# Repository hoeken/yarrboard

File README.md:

# Yarrboard

A collection of open hardware projects for automation projects on your boat.

The project is broken into a few different repositories:

* [FrothFET](https://github.com/hoeken/frothfet) - 8 Channel Digital Switching board with pwm + load monitoring
* [FrothFET Firmware](https://github.com/hoeken/frothfet-firmware) - Firmware for the FrothFET board
* [Brineomatic](https://github.com/hoeken/brineomatic) - Watermaker Controller
* [Brineomatic Firwmare](https://github.com/hoeken/brineomatic) - Firmware for the Brineomatic board
* [SendIt](https://github.com/hoeken/sendit) - 8 channel sensor multitool board
* [SendIt Firwmare](https://github.com/hoeken/sendit-firmware) - Firmware for the SendIt board
* [Yarrboard Framework](https://github.com/hoeken/YarrboardFramework) - Common framework that all the boards run on
* [SignalK Plugin](https://github.com/hoeken/signalk-yarrboard-plugin) - Plugin for SignalK integration
* [Yarrboard Client](https://github.com/hoeken/yarrboard-client) - JS client for controlling a board over websocket

## Interface

Since it is based on the esp32, the main communication method is over WiFi.  Setup, config, and control are very easy using the built-in web portal.  Just point your phone to the url of the board and you're good to go.  Typically this is http://yarrboard.local or http://yarrboard.  You can change this hostname in the settings, or use the IP address instead.

## SignalK

There is also a plugin for integration with SignalK, so you can have your data all in one place.  It supports two way comms, so you can use SignalK and Node-RED to turn your loads on or off.

The plugin for SignalK is called [signalk-yarrboard-plugin](https://github.com/hoeken/signalk-yarrboard-plugin)

## How To Get One

No production as of right now, but possibly in the future.  It is 100% open source, so its possible to order PCBs, parts, and DIY your own board if you like.  There is the potential of partnering with the right person to take care of the manufacturing side of things, or you could make and sell your own - its open source after all!

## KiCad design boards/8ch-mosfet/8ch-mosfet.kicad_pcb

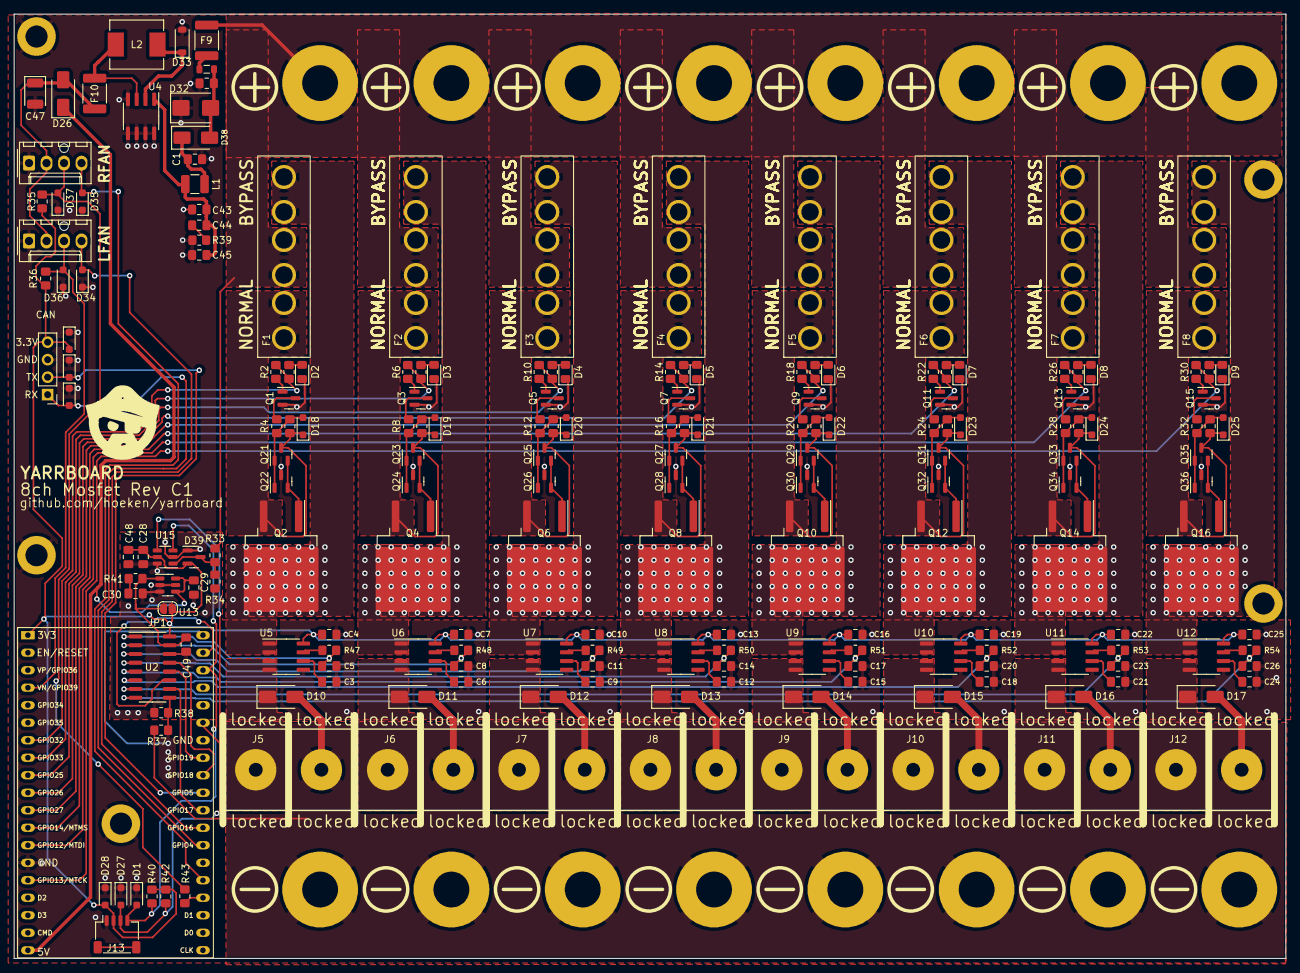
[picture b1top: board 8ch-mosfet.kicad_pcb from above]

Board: 2 copper layers, 184.5 x 137.0 mm, 204 parts (0 on the bottom side), 126 nets.

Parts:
C1: 470nF/50v; C_0805_2012Metric_Pad1.18x1.45mm_HandSolder
C2: 10nF; C_0805_2012Metric_Pad1.18x1.45mm_HandSolder
C3, C6, C9, C12, C15, C18, C21, C24: 1nF; C_0805_2012Metric_Pad1.18x1.45mm_HandSolder
C4, C7, C10, C13, C16, C19, C22, C25, C28, C29, C30, C49: 100nF; C_0805_2012Metric_Pad1.18x1.45mm_HandSolder
C5, C8, C11, C14, C17, C20, C23, C26: 4.7nF; C_0805_2012Metric_Pad1.18x1.45mm_HandSolder
C43: 1uF/50v; C_0805_2012Metric_Pad1.18x1.45mm_HandSolder
C44: 4.7uF/50v; C_0805_2012Metric_Pad1.18x1.45mm_HandSolder
C45: 22uF/35v; C_0805_2012Metric_Pad1.18x1.45mm_HandSolder
C47: 100uF / 10v; CP_EIA-3528-21_Kemet-B
C48: 10uF; C_0805_2012Metric_Pad1.18x1.45mm_HandSolder
D1, D27, D28, D29, D30, D31, D34, D35, D36, D37: PESD3V3L1BA; D_SOD-323_HandSoldering
D2, D3, D4, D5, D6, D7, D8, D9: LED; LED_0805_2012Metric_Pad1.15x1.40mm_HandSolder
D10, D11, D12, D13, D14, D15, D16, D17: SS16; D_SMA
D18, D19, D20, D21, D22, D23, D24, D25: 15V; D_SOD-323_HandSoldering
D26, D38: SX33L; D_SMA
D32: SMBJ30CA; D_SMB
D33: DSK24; D_SOD-123
D39: BAT54S; SOT-23
F1, F2, F3, F4, F5, F6, F7, F8: 25A; ATC Bypass Fuse
F9: mSMD050-60V; Fuse_1812_4532Metric_Pad1.30x3.40mm_HandSolder
F10: mSMD110; Fuse_1812_4532Metric_Pad1.30x3.40mm_HandSolder
FB7: GZ2012D601TF; L_0805_2012Metric
H1, H2, H3, H4, H5: MountingHole; MountingHole_3.2mm_M3_DIN965_Pad
J3: Screw_Terminal_01x08; Busbar 1x9 .375in
J5, J6, J7, J8, J9, J10, J11, J12: Screw_Terminal_01x02; Molex 1x02 .375
J13: I2C; JST_SH_SM04B-SRSS-TB_1x04-1MP_P1.00mm_Horizontal
J14: N2K; PinHeader_1x04_P2.54mm_Vertical
JP1: SolderJumper_2_Open; SolderJumper-2_P1.3mm_Open_RoundedPad1.0x1.5mm
L1: CBC3225T100KR; L_1210_3225Metric
L2: SMMS0650-680M; L_Chilisin_BMRB00060650
LOGO: Logo Small
M1, M2: Fan_4pin; Molex 0470531000
Q1, Q3, Q5, Q7, Q9, Q11, Q13, Q15: 2N7002; SOT-23
Q2, Q4, Q6, Q8, Q10, Q12, Q14, Q16: IPB110P06LM; TO-263-2
Q21, Q23, Q25, Q27, Q29, Q31, Q33, Q35: BC846; SOT-23
Q22, Q24, Q26, Q28, Q30, Q32, Q34, Q36: BC856; SOT-23
R1, R5, R9, R13, R17, R21, R25, R29, R35, R36, R47, R48, R49, R50, R51, R52, R53, R54: 1k; R_0805_2012Metric_Pad1.20x1.40mm_HandSolder
R2, R6, R10, R14, R18, R22, R26, R30: 220R; R_0805_2012Metric_Pad1.20x1.40mm_HandSolder
R3, R7, R11, R15, R19, R23, R27, R31: 27k; R_0805_2012Metric_Pad1.20x1.40mm_HandSolder
R4, R8, R12, R16, R20, R24, R28, R32: 4.7k; R_0805_2012Metric_Pad1.20x1.40mm_HandSolder
R33: 300K 0.1%; R_0805_2012Metric_Pad1.20x1.40mm_HandSolder
R34: 22K 0.1%; R_0805_2012Metric_Pad1.20x1.40mm_HandSolder
R37, R38, R43: 0R; R_0805_2012Metric_Pad1.20x1.40mm_HandSolder
R39: 4.7R; R_0805_2012Metric_Pad1.20x1.40mm_HandSolder
R40, R42: 2.2k; R_0805_2012Metric_Pad1.20x1.40mm_HandSolder
R41: 10k; R_0805_2012Metric_Pad1.20x1.40mm_HandSolder
U1: ESP32-DEVKITC; ESP32-DevKitC
U2: MCP3208; SOIC-16_3.9x9.9mm_P1.27mm
U4: XL1509-5.0; SOIC-8_3.9x4.9mm_P1.27mm
U5, U6, U7, U8, U9, U10, U11, U12: ACS725xLCTR-20AU; ACS7XX
U13: MCP1502-33; SOT-23-6
U15: MCP3425A0T-ECH; SOT-23-6
locked: Screw_Terminal_01x08; Busbar 1x9 .375in

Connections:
+3.3V: C4.1, C7.1, C10.1, C13.1, C16.1, C19.1, C22.1, C25.1, C28.1, C48.1, D28.2 (A2), D31.2 (A2), D39.2 (K), J13.2, J14.4, JP1.2 (B), R35.2, R36.2, R40.2, R42.2, U1.1 (3V3), U2.16 (Vdd), U5.8 (VCC), U6.8 (VCC), U7.8 (VCC), U8.8 (VCC), U9.8 (VCC), U10.8 (VCC), U11.8 (VCC), U12.8 (VCC), U15.5 (Vdd)
+5V: C47.1, D26.2 (A), F10.1, M1.2 (+), M2.2 (+)
+24V: F1.2, F2.2, F3.2, F4.2, F5.2, F6.2, F7.2, F8.2, F9.2, J3.1, J3.2, J3.3, J3.4, J3.5, J3.6, J3.7, J3.8, R33.2
/ADC/A0: C5.1, R47.1, U2.1 (CH0)
/ADC/A1: C8.1, R48.1, U2.2 (CH1)
/ADC/A2: C11.1, R49.1, U2.3 (CH2)
/ADC/A3: C14.1, R50.1, U2.4 (CH3)
/ADC/A4: C17.1, R51.1, U2.5 (CH4)
/ADC/A5: C20.1, R52.1, U2.6 (CH5)
/ADC/A6: C23.1, R53.1, U2.7 (CH6)
/ADC/A7: C26.1, R54.1, U2.8 (CH7)
/CHANNEL 0/PWM: R1.2, R2.1, U1.7 (GPIO32)
/CHANNEL 1/PWM: R5.2, R6.1, U1.8 (GPIO33)
/CHANNEL 2/PWM: R9.2, R10.1, U1.9 (GPIO25)
/CHANNEL 3/PWM: R13.2, R14.1, U1.10 (GPIO26)
/CHANNEL 4/PWM: R17.2, R18.1, U1.11 (GPIO27)
/CHANNEL 5/PWM: R21.2, R22.1, U1.12 (GPIO14)
/CHANNEL 6/PWM: R25.2, R26.1, U1.13 (GPIO12)
/CHANNEL 7/PWM: R29.2, R30.1, U1.15 (GPIO13)
CAN_RX: D29.2 (A2), J14.1, U1.26 (GPIO4)
CAN_TX: D30.2 (A2), J14.2, U1.29 (GPIO5)
ESP32_5V: C29.1, D26.1 (K), U1.19 (5V0), U13.4 (~SHDN), U13.6 (VDD)
FAN_PWM1: D34.2 (A2), M2.4 (PWM), U1.27 (GPIO16)
FAN_PWM2: D35.2 (A2), M1.4 (PWM), U1.24 (GPIO2)
FAN_TACH1: D36.2 (A2), M2.3 (Tacho), R36.1, U1.4 (GPIO39)
FAN_TACH2: D37.2 (A2), M1.3 (Tacho), R35.1, R43.2
GNDA: C3.2, C4.2, C5.2, C6.2, C7.2, C8.2, C9.2, C10.2, C11.2, C12.2, C13.2, C14.2, C15.2, C16.2, C17.2, C18.2, C19.2, C20.2, C21.2, C22.2, C23.2, C24.2, C25.2, C26.2, C28.2, C29.2, C30.2, C48.2, C49.2, D39.1 (A), R34.1, R38.1, U2.14 (AGND), U5.5 (GND), U6.5 (GND), U7.5 (GND), U8.5 (GND), U9.5 (GND), U10.5 (GND), U11.5 (GND), U12.5 (GND), U13.2 (GND), U13.3 (GND), U13.5 (GND), U15.2 (Vss), U15.6 (Vin-)
GNDD: C1.2, C2.2, C43.2, C45.2, C47.2, D1.1 (A1), D2.1 (K), D3.1 (K), D4.1 (K), D5.1 (K), D6.1 (K), D7.1 (K), D8.1 (K), D9.1 (K), D27.1 (A1), D28.1 (A1), D29.1 (A1), D30.1 (A1), D31.1 (A1), D32.1 (A1), D33.2 (A), D34.1 (A1), D35.1 (A1), D36.1 (A1), D37.1 (A1), H1.1, H2.1, H3.1, H4.1, H5.1, J13.1, J14.3, M1.1 (-), M2.1 (-), Q1.2 (S), Q3.2 (S), Q5.2 (S), Q7.2 (S), Q9.2 (S), Q11.2 (S), Q13.2 (S), Q15.2 (S), Q22.3 (C), Q24.3 (C), Q26.3 (C), Q28.3 (C), Q30.3 (C), Q32.3 (C), Q34.3 (C), Q36.3 (C), R37.1, R38.2, R39.2, U1.14 (GND), U1.32 (GND), U1.38 (GND), U2.9 (DGND), U4.4 (~EN), U4.5 (GND), U4.6 (GND), U4.7 (GND), U4.8 (GND)
GNDPWR: D10.2 (A), D11.2 (A), D12.2 (A), D13.2 (A), D14.2 (A), D15.2 (A), D16.2 (A), D17.2 (A), J5.2, J6.2, J7.2, J8.2, J9.2, J10.2, J11.2, J12.2, R37.2, locked.1, locked.2, locked.3, locked.4, locked.5, locked.6, locked.7, locked.8
MISO: U1.31 (GPIO19), U2.12 (Dout)
MOSI: U1.37 (GPIO23), U2.11 (Din)
unnamed: C30.1, R41.1
unnamed: C44.2, R39.1
unnamed: D2.2 (A), R1.1
unnamed: D3.2 (A), R5.1
unnamed: D4.2 (A), R9.1
unnamed: D5.2 (A), R13.1
unnamed: D6.2 (A), R17.1
unnamed: D7.2 (A), R21.1
unnamed: D8.2 (A), R25.1
unnamed: D9.2 (A), R29.1
unnamed: D10.1 (K), J5.1, U5.3 (IP-), U5.4 (IP-)
unnamed: D11.1 (K), J6.1, U6.3 (IP-), U6.4 (IP-)
unnamed: D12.1 (K), J7.1, U7.3 (IP-), U7.4 (IP-)
unnamed: D13.1 (K), J8.1, U8.3 (IP-), U8.4 (IP-)
unnamed: D14.1 (K), J9.1, U9.3 (IP-), U9.4 (IP-)
unnamed: D15.1 (K), J10.1, U10.3 (IP-), U10.4 (IP-)
unnamed: D16.1 (K), J11.1, U11.3 (IP-), U11.4 (IP-)
unnamed: D17.1 (K), J12.1, U12.3 (IP-), U12.4 (IP-)
unnamed: D18.2 (A), Q21.1 (B), Q22.1 (B), R3.1, R4.2
unnamed: D18.1 (K), F1.1, Q2.3 (S), Q21.3 (C), R3.2
unnamed: D19.2 (A), Q23.1 (B), Q24.1 (B), R7.1, R8.2
unnamed: D19.1 (K), F2.1, Q4.3 (S), Q23.3 (C), R7.2
unnamed: D20.2 (A), Q25.1 (B), Q26.1 (B), R11.1, R12.2
unnamed: D20.1 (K), F3.1, Q6.3 (S), Q25.3 (C), R11.2
unnamed: D21.2 (A), Q27.1 (B), Q28.1 (B), R15.1, R16.2
unnamed: D21.1 (K), F4.1, Q8.3 (S), Q27.3 (C), R15.2
unnamed: D22.2 (A), Q29.1 (B), Q30.1 (B), R19.1, R20.2
unnamed: D22.1 (K), F5.1, Q10.3 (S), Q29.3 (C), R19.2
unnamed: D23.2 (A), Q31.1 (B), Q32.1 (B), R23.1, R24.2
unnamed: D23.1 (K), F6.1, Q12.3 (S), Q31.3 (C), R23.2
unnamed: D24.2 (A), Q33.1 (B), Q34.1 (B), R27.1, R28.2
unnamed: D24.1 (K), F7.1, Q14.3 (S), Q33.3 (C), R27.2
unnamed: D25.2 (A), Q35.1 (B), Q36.1 (B), R31.1, R32.2
unnamed: D25.1 (K), F8.1, Q16.3 (S), Q35.3 (C), R31.2
unnamed: C2.1, D32.2 (A2), D38.2 (A), FB7.2
unnamed: D33.1 (K), L2.1, U4.2 (OUT)
unnamed: C1.1, D38.1 (K), L1.1
unnamed: D39.3 (COM), R33.1, R34.2, U15.1 (Vin+)
unnamed: F9.1, FB7.1
unnamed: Q1.3 (D), R4.1
unnamed: Q1.1 (G), R2.2
unnamed: F1.3, Q2.2 (D), U5.1 (IP+), U5.2 (IP+)
unnamed: Q2.1 (G), Q21.2 (E), Q22.2 (E)
unnamed: Q3.3 (D), R8.1
unnamed: Q3.1 (G), R6.2
unnamed: F2.3, Q4.2 (D), U6.1 (IP+), U6.2 (IP+)
unnamed: Q5.3 (D), R12.1
unnamed: Q5.1 (G), R10.2
unnamed: F3.3, Q6.2 (D), U7.1 (IP+), U7.2 (IP+)
unnamed: Q7.3 (D), R16.1
unnamed: Q7.1 (G), R14.2
unnamed: F4.3, Q8.2 (D), U8.1 (IP+), U8.2 (IP+)
unnamed: Q9.3 (D), R20.1
unnamed: Q9.1 (G), R18.2
unnamed: F5.3, Q10.2 (D), U9.1 (IP+), U9.2 (IP+)
unnamed: Q10.1 (G), Q29.2 (E), Q30.2 (E)
unnamed: Q11.3 (D), R24.1
unnamed: Q11.1 (G), R22.2
unnamed: F6.3, Q12.2 (D), U10.1 (IP+), U10.2 (IP+)
unnamed: Q12.1 (G), Q31.2 (E), Q32.2 (E)
unnamed: Q13.3 (D), R28.1
unnamed: Q13.1 (G), R26.2
unnamed: F7.3, Q14.2 (D), U11.1 (IP+), U11.2 (IP+)
unnamed: Q14.1 (G), Q33.2 (E), Q34.2 (E)
unnamed: Q15.3 (D), R32.1
unnamed: Q15.1 (G), R30.2
unnamed: F8.3, Q16.2 (D), U12.1 (IP+), U12.2 (IP+)
unnamed: Q16.1 (G), Q35.2 (E), Q36.2 (E)
unnamed: Q4.1 (G), Q23.2 (E), Q24.2 (E)
unnamed: Q6.1 (G), Q25.2 (E), Q26.2 (E)
unnamed: Q8.1 (G), Q27.2 (E), Q28.2 (E)
unnamed: R43.1, U1.23 (GPIO15)
unnamed: F10.2, L2.2, U4.3 (FB)
unnamed: C43.1, C44.1, C45.1, L1.2, U4.1 (VIN)
unnamed: C3.1, U5.6 (FILTER)
unnamed: R47.2, U5.7 (VIOUT)
unnamed: C6.1, U6.6 (FILTER)
unnamed: R48.2, U6.7 (VIOUT)
unnamed: C9.1, U7.6 (FILTER)
unnamed: R49.2, U7.7 (VIOUT)
unnamed: C12.1, U8.6 (FILTER)
unnamed: R50.2, U8.7 (VIOUT)
unnamed: C15.1, U9.6 (FILTER)
unnamed: R51.2, U9.7 (VIOUT)
unnamed: C18.1, U10.6 (FILTER)
unnamed: R52.2, U10.7 (VIOUT)
unnamed: C21.1, U11.6 (FILTER)
unnamed: R53.2, U11.7 (VIOUT)
unnamed: C24.1, U12.6 (FILTER)
unnamed: R54.2, U12.7 (VIOUT)
REF_3V3: C49.1, JP1.1 (A), R41.2, U2.15 (Vref), U13.1 (OUT)
SCK: U1.30 (GPIO18), U2.13 (CLK)
SCL: D1.2 (A2), J13.4, R40.1, U1.36 (GPIO22), U15.3 (SCL)
SDA: D27.2 (A2), J13.3, R42.1, U1.33 (GPIO21), U15.4 (SDA)
SS: U1.28 (GPIO17), U2.10 (~CS/SHDN)

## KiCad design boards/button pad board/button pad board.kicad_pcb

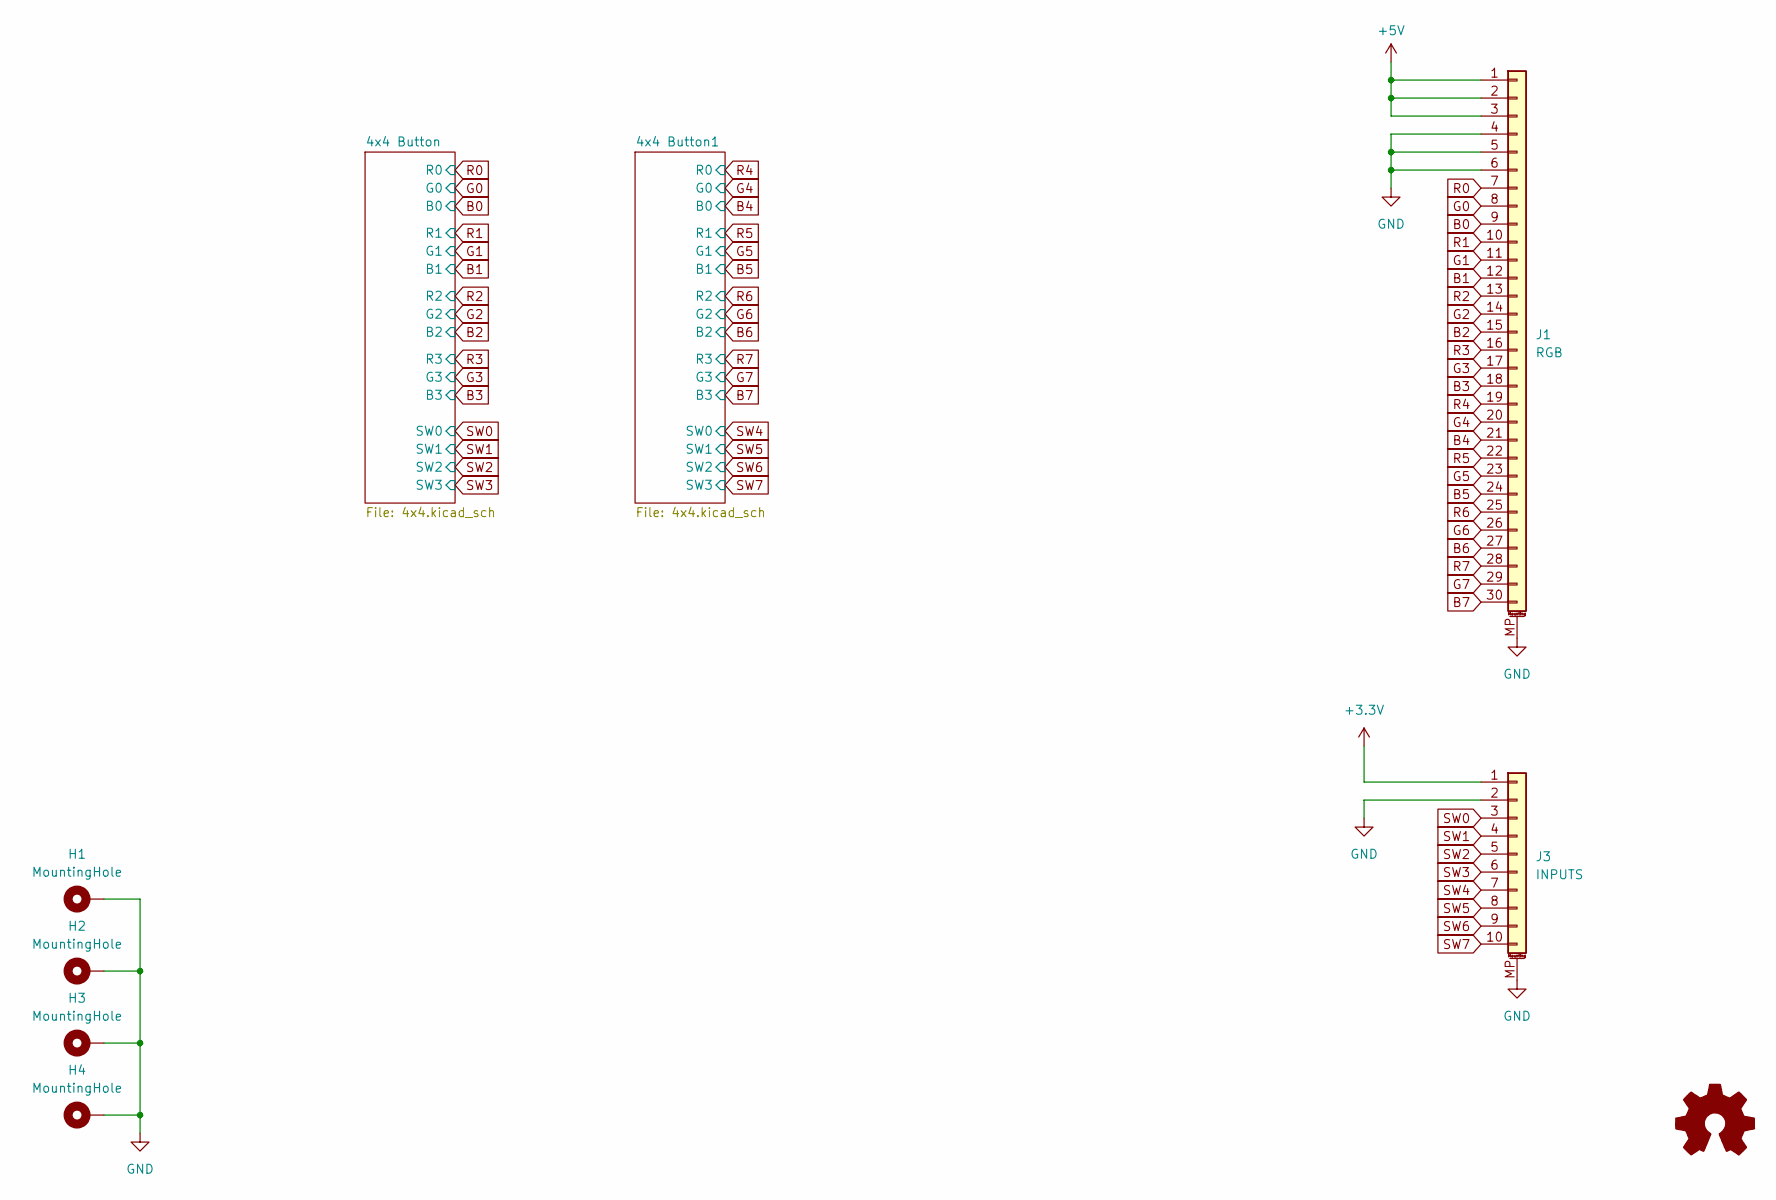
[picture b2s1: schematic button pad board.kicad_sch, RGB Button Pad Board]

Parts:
H1, H2, H3, H4: MountingHole; MountingHole_3.2mm_M3_DIN965_Pad
J1: RGB; TE_3-84952-0_1x30-1MP_P1.0mm_Horizontal; LCSC C262358
J3: INPUTS; TE_1-84952-0_1x10-1MP_P1.0mm_Horizontal; LCSC C262385 or C52162

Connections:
+3.3V: J3.1
+5V: J1.1, J1.2, J1.3; also elsewhere on the board
B0: J1.9; also elsewhere on the board
B1: J1.12; also elsewhere on the board
B2: J1.15; also elsewhere on the board
B3: J1.18; also elsewhere on the board
B4: J1.21; also elsewhere on the board
B5: J1.24; also elsewhere on the board
B6: J1.27; also elsewhere on the board
B7: J1.30; also elsewhere on the board
G0: J1.8; also elsewhere on the board
G1: J1.11; also elsewhere on the board
G2: J1.14; also elsewhere on the board
G3: J1.17; also elsewhere on the board
G4: J1.20; also elsewhere on the board
G5: J1.23; also elsewhere on the board
G6: J1.26; also elsewhere on the board
G7: J1.29; also elsewhere on the board
GND: H1.1, H2.1, H3.1, H4.1, J1.4, J1.5, J1.6, J1.MP (MountPin), J3.2, J3.MP (MountPin); also elsewhere on the board
R0: J1.7; also elsewhere on the board
R1: J1.10; also elsewhere on the board
R2: J1.13; also elsewhere on the board
R3: J1.16; also elsewhere on the board
R4: J1.19; also elsewhere on the board
R5: J1.22; also elsewhere on the board
R6: J1.25; also elsewhere on the board
R7: J1.28; also elsewhere on the board
SW0: J3.3; also elsewhere on the board
SW1: J3.4; also elsewhere on the board
SW2: J3.5; also elsewhere on the board
SW3: J3.6; also elsewhere on the board
SW4: J3.7; also elsewhere on the board
SW5: J3.8; also elsewhere on the board
SW6: J3.9; also elsewhere on the board
SW7: J3.10; also elsewhere on the board

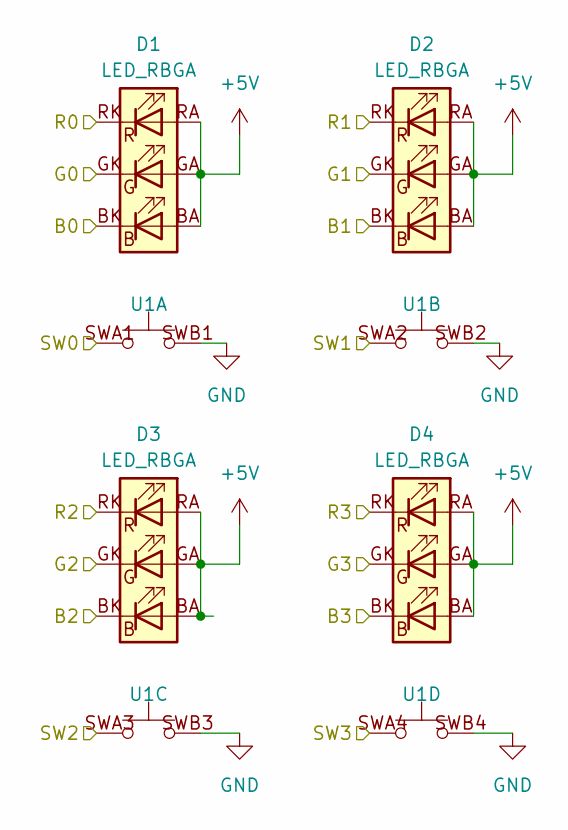
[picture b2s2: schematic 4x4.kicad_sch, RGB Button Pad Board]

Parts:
D1, D2, D3, D4: LED_RBGA; WURTH_LED_RGB_5050-6; LCSC C784540
U1: BUTTONPAD-2X2; Mouser 474-COM-07836

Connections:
+5V: D1.BA, D1.GA, D1.RA, D2.BA, D2.GA, D2.RA, D3.BA, D3.GA, D3.RA, D4.BA, D4.GA, D4.RA; also elsewhere on the board
B0: D1.BK; also elsewhere on the board
B1: D2.BK; also elsewhere on the board
B2: D3.BK; also elsewhere on the board
B3: D4.BK; also elsewhere on the board
G0: D1.GK; also elsewhere on the board
G1: D2.GK; also elsewhere on the board
G2: D3.GK; also elsewhere on the board
G3: D4.GK; also elsewhere on the board
GND: U1.SWB1, U1.SWB2, U1.SWB3, U1.SWB4; also elsewhere on the board
R0: D1.RK; also elsewhere on the board
R1: D2.RK; also elsewhere on the board
R2: D3.RK; also elsewhere on the board
R3: D4.RK; also elsewhere on the board
SW0: U1.SWA1; also elsewhere on the board
SW1: U1.SWA2; also elsewhere on the board
SW2: U1.SWA3; also elsewhere on the board
SW3: U1.SWA4; also elsewhere on the board

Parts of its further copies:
D5, D6, D7, D8: LED_RBGA; WURTH_LED_RGB_5050-6; LCSC C784540
U2: BUTTONPAD-2X2; Mouser 474-COM-07836

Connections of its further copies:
+5V: D5.BA, D5.GA, D5.RA, D6.BA, D6.GA, D6.RA, D7.BA, D7.GA, D7.RA, D8.BA, D8.GA, D8.RA; also elsewhere on the board
B4: D5.BK; also elsewhere on the board
B5: D6.BK; also elsewhere on the board
B6: D7.BK; also elsewhere on the board
B7: D8.BK; also elsewhere on the board
G4: D5.GK; also elsewhere on the board
G5: D6.GK; also elsewhere on the board
G6: D7.GK; also elsewhere on the board
G7: D8.GK; also elsewhere on the board
GND: U2.SWB1, U2.SWB2, U2.SWB3, U2.SWB4; also elsewhere on the board
R4: D5.RK; also elsewhere on the board
R5: D6.RK; also elsewhere on the board
R6: D7.RK; also elsewhere on the board
R7: D8.RK; also elsewhere on the board
SW4: U2.SWA1; also elsewhere on the board
SW5: U2.SWA2; also elsewhere on the board
SW6: U2.SWA3; also elsewhere on the board
SW7: U2.SWA4; also elsewhere on the board

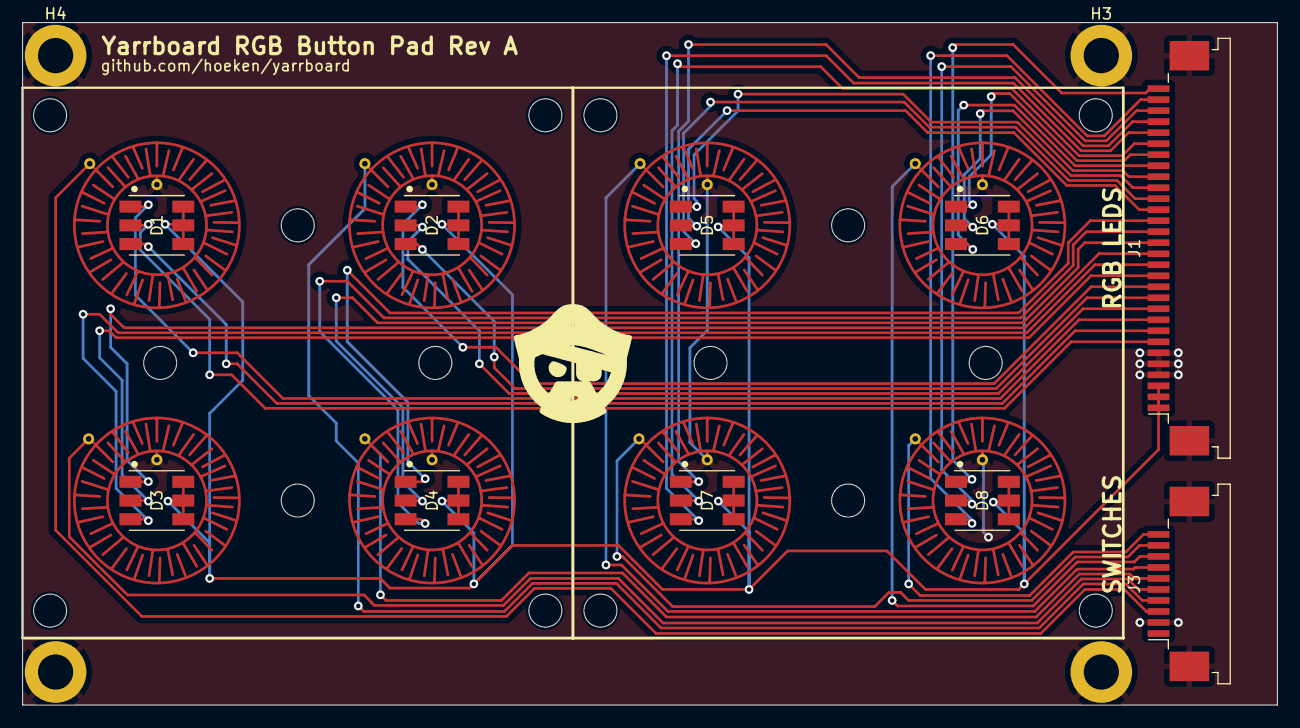
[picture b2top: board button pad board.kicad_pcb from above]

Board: 2 copper layers, 114.0 x 62.0 mm, 16 parts (0 on the bottom side), 34 nets.

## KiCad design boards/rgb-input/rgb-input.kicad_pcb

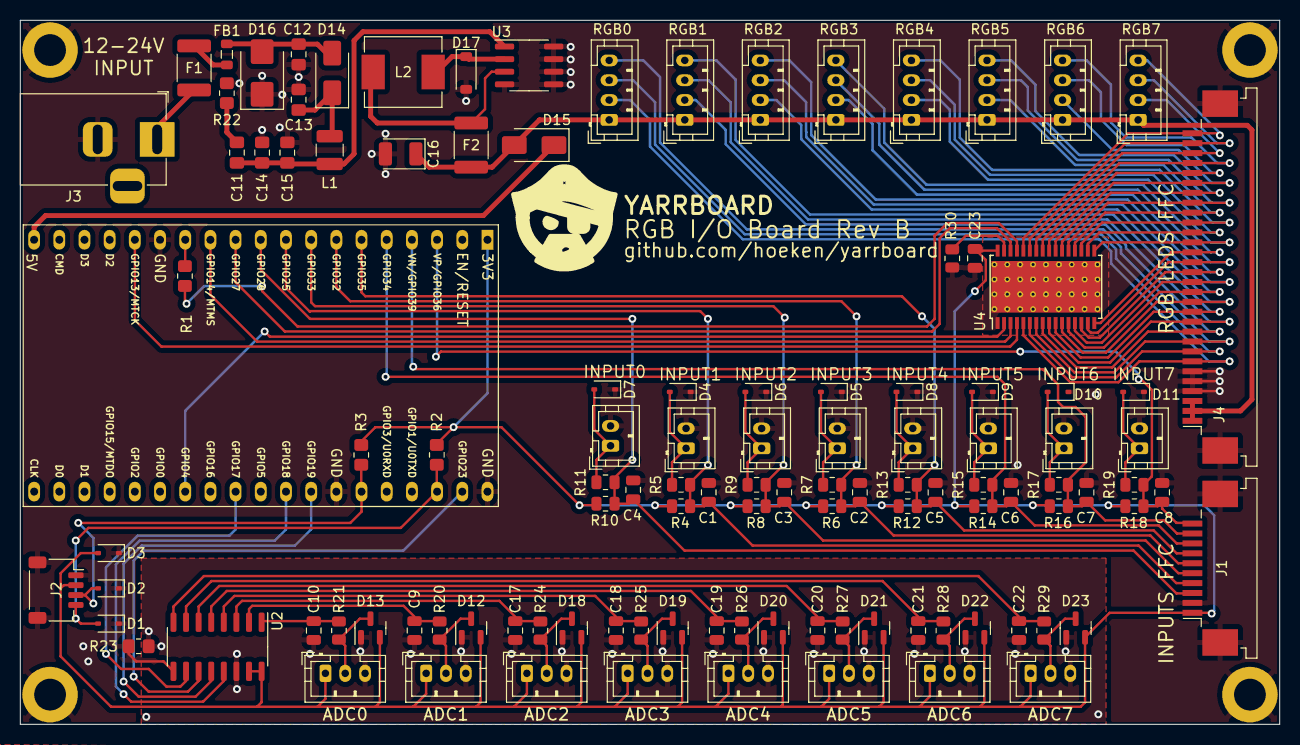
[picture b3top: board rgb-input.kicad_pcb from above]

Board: 2 copper layers, 127.0 x 71.0 mm, 118 parts (0 on the bottom side), 82 nets.

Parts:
ADC0, ADC1, ADC2, ADC3, ADC4, ADC5, ADC6, ADC7: JST_PH_B3B-PH-K_1x03_P2.00mm_Vertical
C1, C2, C3, C4, C5, C6, C7, C8, C9, C10, C17, C18, C19, C20, C21, C22: 10nF; C_0805_2012Metric
C11: 4.7uF/50v; C_0805_2012Metric_Pad1.18x1.45mm_HandSolder
C12: 10nF; C_0805_2012Metric_Pad1.18x1.45mm_HandSolder
C13: 470nF/50v; C_0805_2012Metric_Pad1.18x1.45mm_HandSolder
C14: 1uF/50v; C_0805_2012Metric_Pad1.18x1.45mm_HandSolder
C15: 22uF/35v; C_0805_2012Metric_Pad1.18x1.45mm_HandSolder
C16: 100uF/10v; CP_EIA-3528-21_Kemet-B
C23: 10uF; C_0805_2012Metric
D1, D2, D3, D4, D5, D6, D7, D8, D9, D10, D11: PESD3V3L1BA; D_SOD-323
D12, D13, D18, D19, D20, D21, D22, D23: BAT54S; SOT-23
D14, D15: SX33L; D_SMA
D16: SMBJ30CA; D_SMB
D17: DSK24; D_SOD-123
F1: mSMD050-60V; Fuse_1812_4532Metric_Pad1.30x3.40mm_HandSolder
F2: mSMD110; Fuse_1812_4532Metric_Pad1.30x3.40mm_HandSolder
FB1: GZ2012D601TF; L_0805_2012Metric
H1, H2, H3, H4: MountingHole; MountingHole_3.2mm_M3_DIN965_Pad
INPUT0, INPUT1, INPUT2, INPUT3, INPUT4, INPUT5, INPUT6, INPUT7: JST_PH_B2B-PH-K_1x02_P2.00mm_Vertical
J1: INPUTS; TE_1-84952-0_1x10-1MP_P1.0mm_Horizontal
J2: I2C; JST_SH_SM04B-SRSS-TB_1x04-1MP_P1.00mm_Horizontal
J3: Barrel_Jack; BarrelJack_Horizontal
J4: RGB; TE_3-84952-0_1x30-1MP_P1.0mm_Horizontal
L1: CBC3225T100KR; L_1210_3225Metric
L2: SMMS0650-680M; L_Chilisin_BMRB00060650
LOGO: Logo Small
R1, R23: 0R; R_0805_2012Metric_Pad1.20x1.40mm_HandSolder
R2, R3: 2.2k; R_0805_2012Metric_Pad1.20x1.40mm_HandSolder
R4, R6, R8, R10, R12, R14, R16, R18: 100k; R_0805_2012Metric
R5, R7, R9, R11, R13, R15, R17, R19, R20, R21, R24, R25, R26, R27, R28, R29: 1k; R_0805_2012Metric
R22: 4.7R; R_0805_2012Metric_Pad1.20x1.40mm_HandSolder
R30: 3.3k; R_0805_2012Metric
RGB0, RGB1, RGB2, RGB3, RGB4, RGB5, RGB6, RGB7: JST_PH_B4B-PH-K_1x04_P2.00mm_Vertical
U1: ESP32-DEVKITC; ESP32-DevKitC
U2: MCP3208; SOIC-16_3.9x9.9mm_P1.27mm
U3: XL1509-5.0; SOIC-8_3.9x4.9mm_P1.27mm
U4: TLC5947DAP; HTSSOP-32-1EP_6.1x11mm_P0.65mm_EP5.2x11mm_Mask4.11x4.36mm_T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

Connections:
+3.3V: ADC0.1, ADC1.1, ADC2.1, ADC3.1, ADC4.1, ADC5.1, ADC6.1, ADC7.1, C23.1, D3.2 (A2), D12.2 (K), D13.2 (K), D18.2 (K), D19.2 (K), D20.2 (K), D21.2 (K), D22.2 (K), D23.2 (K), J1.1, J2.2, R2.2, R3.2, R4.1, R6.1, R8.1, R10.1, R12.1, R14.1, R16.1, R18.1, U1.1 (3V3), U2.15 (Vref), U2.16 (Vdd), U4.32 (VCC)
+5V: C16.1, D15.2 (A), F2.1, J4.1, J4.2, J4.3, RGB0.1, RGB1.1, RGB2.1, RGB3.1, RGB4.1, RGB5.1, RGB6.1, RGB7.1
+24V: F1.2, J3.1
/ADC Input0/INPUT: C10.1, R21.2, U2.1 (CH0)
/ADC Input1/INPUT: C9.1, R20.2, U2.2 (CH1)
/ADC Input2/INPUT: C17.1, R24.2, U2.3 (CH2)
/ADC Input3/INPUT: C18.1, R25.2, U2.4 (CH3)
/ADC Input4/INPUT: C19.1, R26.2, U2.5 (CH4)
/ADC Input5/INPUT: C20.1, R27.2, U2.6 (CH5)
/ADC Input6/INPUT: C21.1, R28.2, U2.7 (CH6)
/ADC Input7/INPUT: C22.1, R29.2, U2.8 (CH7)
/INPUT0: C4.1, J1.3, R10.2, R11.2, U1.10 (GPIO26)
/INPUT1: C1.1, J1.4, R4.2, R5.2, U1.9 (GPIO25)
/INPUT2: C3.1, J1.5, R8.2, R9.2, U1.8 (GPIO33)
/INPUT3: C2.1, J1.6, R6.2, R7.2, U1.7 (GPIO32)
/INPUT4: C5.1, J1.7, R12.2, R13.2, U1.6 (GPIO35)
/INPUT5: C6.1, J1.8, R14.2, R15.2, U1.5 (GPIO34)
/INPUT6: C7.1, J1.9, R16.2, R17.2, U1.4 (GPIO39)
/INPUT7: C8.1, J1.10, R18.2, R19.2, U1.3 (GPIO36)
/LEDS/BLUE0: J4.9, RGB0.4, U4.7 (OUT2)
/LEDS/BLUE1: J4.12, RGB1.4, U4.10 (OUT5)
/LEDS/BLUE2: J4.15, RGB2.4, U4.13 (OUT8)
/LEDS/BLUE3: J4.18, RGB3.4, U4.16 (OUT11)
/LEDS/BLUE4: J4.21, RGB4.4, U4.19 (OUT14)
/LEDS/BLUE5: J4.24, RGB5.4, U4.22 (OUT17)
/LEDS/BLUE6: J4.27, RGB6.4, U4.25 (OUT20)
/LEDS/BLUE7: J4.30, RGB7.4, U4.28 (OUT23)
/LEDS/GREEN0: J4.8, RGB0.3, U4.6 (OUT1)
/LEDS/GREEN1: J4.11, RGB1.3, U4.9 (OUT4)
/LEDS/GREEN2: J4.14, RGB2.3, U4.12 (OUT7)
/LEDS/GREEN3: J4.17, RGB3.3, U4.15 (OUT10)
/LEDS/GREEN4: J4.20, RGB4.3, U4.18 (OUT13)
/LEDS/GREEN5: J4.23, RGB5.3, U4.21 (OUT16)
/LEDS/GREEN6: J4.26, RGB6.3, U4.24 (OUT19)
/LEDS/GREEN7: J4.29, RGB7.3, U4.27 (OUT22)
/LEDS/RED0: J4.7, RGB0.2, U4.5 (OUT0)
/LEDS/RED1: J4.10, RGB1.2, U4.8 (OUT3)
/LEDS/RED2: J4.13, RGB2.2, U4.11 (OUT6)
/LEDS/RED3: J4.16, RGB3.2, U4.14 (OUT9)
/LEDS/RED4: J4.19, RGB4.2, U4.17 (OUT12)
/LEDS/RED5: J4.22, RGB5.2, U4.20 (OUT15)
/LEDS/RED6: J4.25, RGB6.2, U4.23 (OUT18)
/LEDS/RED7: J4.28, RGB7.2, U4.26 (OUT21)
ADC_MISO: U1.31 (GPIO19), U2.12 (Dout)
ADC_MOSI: U1.37 (GPIO23), U2.11 (Din)
ADC_SCK: U1.30 (GPIO18), U2.13 (CLK)
ADC_SS: U1.28 (GPIO17), U2.10 (~CS/SHDN)
ESP32_VIN: D15.1 (K), U1.19 (5V0)
GNDA: ADC0.3, ADC1.3, ADC2.3, ADC3.3, ADC4.3, ADC5.3, ADC6.3, ADC7.3, C9.2, C10.2, C17.2, C18.2, C19.2, C20.2, C21.2, C22.2, D12.1 (A), D13.1 (A), D18.1 (A), D19.1 (A), D20.1 (A), D21.1 (A), D22.1 (A), D23.1 (A), R23.1, U2.14 (AGND)
GNDD: C1.2, C2.2, C3.2, C4.2, C5.2, C6.2, C7.2, C8.2, C12.2, C13.2, C14.2, C15.2, C16.2, C23.2, D1.1 (A1), D2.1 (A1), D3.1 (A1), D4.1 (A1), D5.1 (A1), D6.1 (A1), D7.1 (A1), D8.1 (A1), D9.1 (A1), D10.1 (A1), D11.1 (A1), D16.1 (A1), D17.2 (A), H1.1, H2.1, H3.1, H4.1, INPUT0.2, INPUT1.2, INPUT2.2, INPUT3.2, INPUT4.2, INPUT5.2, INPUT6.2, INPUT7.2, J1.2, J1.MP (MountPin), J2.1, J2.MP (MountPin), J3.2, J4.4, J4.5, J4.6, J4.MP (MountPin), R22.2, R23.2, R30.2, U1.14 (GND), U1.32 (GND), U1.38 (GND), U2.9 (DGND), U3.4 (~EN), U3.5 (GND), U3.6 (GND), U3.7 (GND), U3.8 (GND), U4.1 (GND), U4.33 (PowerPAD)
LED_BLANK: U1.26 (GPIO4), U4.2 (BLANK)
LED_MISO: R1.2, U4.29 (SOUT)
LED_MOSI: U1.15 (GPIO13), U4.4 (SIN)
LED_SCK: U1.12 (GPIO14), U4.3 (SCLK)
LED_SS: U1.11 (GPIO27), U4.30 (XLAT)
unnamed: ADC0.2, D13.3 (COM), R21.1
unnamed: ADC1.2, D12.3 (COM), R20.1
unnamed: ADC2.2, D18.3 (COM), R24.1
unnamed: ADC3.2, D19.3 (COM), R25.1
unnamed: ADC4.2, D20.3 (COM), R26.1
unnamed: ADC5.2, D21.3 (COM), R27.1
unnamed: ADC6.2, D22.3 (COM), R28.1
unnamed: ADC7.2, D23.3 (COM), R29.1
unnamed: C11.2, R22.1
unnamed: D4.2 (A2), INPUT1.1, R5.1
unnamed: D5.2 (A2), INPUT3.1, R7.1
unnamed: D6.2 (A2), INPUT2.1, R9.1
unnamed: D7.2 (A2), INPUT0.1, R11.1
unnamed: D8.2 (A2), INPUT4.1, R13.1
unnamed: D9.2 (A2), INPUT5.1, R15.1
unnamed: D10.2 (A2), INPUT6.1, R17.1
unnamed: D11.2 (A2), INPUT7.1, R19.1
unnamed: C12.1, D14.2 (A), D16.2 (A2), FB1.2
unnamed: C13.1, D14.1 (K), L1.1
unnamed: D17.1 (K), L2.1, U3.2 (OUT)
unnamed: F1.1, FB1.1
unnamed: R1.1, U1.13 (GPIO12)
unnamed: F2.2, L2.2, U3.3 (FB)
unnamed: C11.1, C14.1, C15.1, L1.2, U3.1 (VIN)
unnamed: R30.1, U4.31 (IREF)
SCL: D1.2 (A2), J2.4, R2.1, U1.36 (GPIO22)
SDA: D2.2 (A2), J2.3, R3.1, U1.33 (GPIO21)

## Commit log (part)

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2023-07-27 some tidying
2023-07-27 updated gitignore
2023-07-27 changed project name to yarrboard
2023-07-27 more renaming
2023-07-27 moving day!
2023-07-27 lots of moving
2023-07-27 vscode stuff
2023-07-27 fixed firmware url
2023-07-27 make a baseline release.
2023-07-27 update todo
2023-07-27 todo
2023-07-27 updated the stackup doc
2023-07-27 new firmware update notice looking good.
2023-07-28 Yes! OTA is working nicely with feedback now.
2023-07-28 starting refactor. going to be a beast
2023-07-28 okay version checking working a little bit better
2023-07-28 testing firmware signing and release process
2023-07-28 ugh this ota stuff sucks
2023-08-01 quick bump to check ota
2023-08-01 okay, ota is working well enough for now.
2023-08-01 updated footprints, changed 5v diode, and added jumpers for fan voltage
2023-08-01 mosfet driver resistors updated, looking good now.
2023-08-01 added 2nd fan header and simplified circuit.
2023-08-02 expanded current to 2 decimals
2023-08-02 changes to the lid
2023-08-02 added a better adc for getting bus voltage
2023-08-02 minor update change
2023-08-02 fixed bug with config UI
2023-08-02 slight changes to FOTA
2023-08-02 ota ota ota
2023-08-02 ota 34444
2023-08-02 added images.
2023-08-02 added closeup image.
2023-08-02 typo
2023-08-02 config system seems to be working
2023-08-03 absolutely massive refactor.
2023-08-03 fixed a minor bug with mdns
2023-08-03 added fans info to stats and to the web ui.
2023-08-03 renamed websocket to server
2023-08-03 added project header
2023-08-03 moved channel pwm setup to config
2023-08-04 another big refactor to break the networking apart from the protocol
2023-08-04 noice. we can send json to serial port now.
2023-08-04 okay web server options looking very nice.
2023-08-04 nice. the api is definitely doable now!
2023-08-04 absolutely loving the post-refactor code.
2023-08-04 oh yeah. serial port working now too.
2023-08-04 refactor to clean up the handlereceivedjson function
2023-08-04 app and network prefs separated. flags for serial and web api.
2023-08-04 Update README.md
    added protocol info.
2023-08-04 minor ui bug
2023-08-04 Update README.md
    more protocol docs
2023-08-04 Update README.md
    couple fixes
2023-08-04 fixed a bug with saving prefs
2023-08-04 changed back to default url for client
2023-08-04 added bus voltage to main page
2023-08-04 added a toggle channel state to the protocol
2023-08-05 made response buffer a bit smaller
2023-08-05 a few updates to the strlcpy calls
2023-08-05 a couple fixes to the fade script.
2023-08-05 updated case design
2023-08-05 testing led fader
2023-08-05 more case design
2023-08-05 changed to thread safe channel fade call.
2023-08-06 pretty sure i figured out the crashing.
2023-08-06 client testing updates
2023-08-06 updated client code
2023-08-06 added timing code to the server. found the slow one.
2023-08-06 successful refactor to JsonVariant
2023-08-06 http api working again now too.
2023-08-06 we can now have empty messages
2023-08-06 client updates
2023-08-06 yes, its working nicely now. yay!
2023-08-06 changed to fifo on websocket request parsing
2023-08-06 finally refactored channel into its own class
2023-08-06 updated state on fade
2023-08-07 updated error and success code json format
2023-08-07 added msg field to status replies
2023-08-07 converted to yarrboard-client npm
2023-08-07 renamed folder
2023-08-07 some tweaks to the channel fade for better UI response
2023-08-07 message tracking enabled
2023-08-07 tester updates
2023-08-07 case design is almost complete
2023-08-07 added design for terminal cover
2023-08-07 updated schematic
2023-08-08 a couple mods to the case
2023-08-08 removed the mcp3x21 library
2023-08-08 updated terminal cover with pos and neg graphics
2023-08-08 added logo and fixed terminal cover neg
2023-08-08 changed the neg sign
2023-08-08 a couple tweaks to mosfet circuit
2023-08-08 updated the adc schematic a bit
2023-08-09 fixed a bug with the ADC soft fuse
2023-08-09 moved pos/neg to top of case
2023-08-09 adc code now does very fast amp checking and averaging between messages
2023-08-09 yes! duty cycle ui and functions are working well
2023-08-09 added zip tie mounts to the case design
2023-08-09 upgraded the i2c/serial connectors + power based on the sailor hat schematic
2023-08-10 more or less placed all the stuff that needs to be placed
2023-08-10 whew, lots of routing.
2023-08-10 fixed drc errors, just silkscreen left
2023-08-10 added in reverse polarity diode to power circuit
2023-08-10 silkscreen almost complete
2023-08-10 updated schematic to pass erc
2023-08-10 moved case design to its own folder
2023-08-10 lowered delay
2023-08-10 added the rgb input board.
2023-08-11 fixed a part number
2023-08-11 enabled sleep mode
2023-08-11 this board is going to be sick.
2023-08-12 tested the bus voltage stuff a bit more
2023-08-12 changed wifi code again
2023-08-12 figured out most of the components, working on placement
2023-08-13 more layout checks on the input board
2023-08-13 changed voltage regulator to smt
2023-08-13 changed back to qwiic and moved it under the esp32
2023-08-13 routed the rgb setup
2023-08-13 moved our test functions outside onopen - spawning too many 'threads'
2023-08-13 too much routing
2023-08-14 whoa, board is fully routed!!!!
2023-08-14 moved out library to its own folder
2023-08-14 moved to a shared library
2023-08-14 started on button pad board.
2023-08-14 oh yeah, looking good.
2023-08-14 more crashes
2023-08-22 added 5v fuse to schematic
2023-10-16 prepared 8ch mosfet for production
2023-10-16 added pcb changes.
2023-10-16 a couple more tweaks to rgb input.
2023-10-16 moved some app config stuff to protocol
2023-10-16 small bit of server refactor
2023-10-18 updated BOM
2023-10-18 updated tester to be a bit more chill
2023-10-18 more BOM updates.
2023-10-18 fixed a bug with setting up the network
2023-10-18 oops, debug code
2023-10-19 ignore log file
2023-10-19 worked on the button board a bit
2023-10-19 changed to 5050 led for interface board
2023-10-19 some debugging tests
2023-10-19 damnit, messed up the sda/scl lines on the board
2023-10-19 added note for webserver fork
2023-10-20 more aggressive tester
2023-10-20 increased slow message time and changed to new library
2023-10-20 thinking about how to remove spiffs + found an adc library
2023-10-20 more debugging
2023-10-20 Fixed a bug where setup would hang on the reboot after a crash
2023-10-24 updated testing scripts
2023-10-24 a bit of work to get ready for the rev b boards
2023-10-24 updated more configs to use YB_ prefix on defines
2023-10-24 more prep and cleaning for the new boards
2023-10-24 started work on input code for rgb input board
2023-10-25 started work on inputs
2023-10-25 added input channels to protocol
2023-10-25 moved bus voltage to own files
2023-10-25 stupid ota spiffs pragma message is annoying
2023-10-25 sick! removed the requirement for SPIFFS
2023-10-25 more work to remove requirement for spiffs!
2023-10-25 so much more space with a small SPIFFS partition.
2023-10-25 cleanup
2023-10-25 started on the rgb channels framework
2023-10-25 updated some channel pref names/keys
2023-10-26 added the basic code for writing to the led driver
2023-10-26 added init
2023-10-26 added library code for the bus adc
2023-10-26 updated from outputchannel to pwmchannel
2023-10-26 updated input channel defines
2023-10-26 updated adc defines
2023-10-26 comment
2023-10-26 massive channel -> pwm search and replace
2023-10-26 ok hopefully rgb stuff will be a bit more efficient now
2023-10-26 yes! new bus voltage circuit is working.
2023-10-26 removed mouser p/n
2023-10-26 moved decimal place on current measurement
2023-10-27 damn, found an issue with my pinouts
2023-10-27 fighting json bug... good state now.
2023-10-27 a few more changes before bed.
2023-10-27 updated inductor footprint
2023-10-27 fixed login page missing image
2023-10-27 input, rgb, and adc all populating now.
2023-10-27 solved the ADC issue and found another minor one
2023-10-27 some updates to the UI
2023-10-27 Channel config is working + rgb selection working
2023-10-27 updated todo
2023-10-27 added new board to firmware update file
2023-10-27 worked on changes to input rev b
2023-10-27 rgb is working
2023-10-28 got to the bottom of the current measurement noise
2023-10-28 updated the config UI to new style
2023-10-28 fans tested as working, needs fix though.
2023-10-28 updated mosfet driver schematic with changes
2023-10-28 first pass on redesign of the rgb input board
2023-10-28 new rgb input board coming along very nicely
2023-10-29 new rgb input board is starting to look very nice.
2023-10-29 passing ERC and DRC
2023-10-29 reannotated and did some more cleanup. almost ready
2023-10-29 starting a redesign ahead of having parts to test. wish me luck
2023-10-29 reannotated
2023-10-29 worked on the new layout. hope the gate driver works
2023-10-29 mosfet board looking good too
2023-10-29 button board updated, routed, and ready to rock.
2023-10-30 first commit of the 'totem pole' driver design
2023-10-30 oof, working from the wrong copy, had to redo some stuff
2023-10-30 changed p/n
2023-10-30 update some of our todos
2023-10-30 found a tiny issue
2023-10-30 fixed the led / pwm issue. yay!
2023-10-30 moved the tester back to firmware folder for ease of dev
2023-10-30 moved tester folder to firmware for dev work
2023-10-30 crap, checked in the node_modules. oops
2023-10-30 status page now comes back from a reconnect
2023-10-30 dynamic pwm slider works really smoothly now
2023-10-30 worked on the fans and have a plan for the fan.
2023-10-31 added wattage to pwm mosfet UI
2023-10-31 very large staticjson still causes crashes
2023-10-31 updated TLC5947 driver to use hardware SPI. yay!
2023-10-31 slowly figuring out how to automate the release process
2023-10-31 okay that was easy
2023-10-31 new firmware relase script
2023-10-31 consolidated board names
2023-10-31 more test changes for ota
2023-10-31 more ota testing
2023-10-31 yes! ota is back to working again lol
2023-10-31 testing signature ota now
2023-10-31 ugh more testing
2023-10-31 if this works were golden
2023-10-31 moar testing!
2023-10-31 first release housekeeping
2023-11-01 more release automation
2023-11-01 Firmware release v1.0.1
2023-11-01 added a few late night ideas
2023-11-01 idea update
2023-11-01 added template files for the new board revs
2023-11-01 forgot a file
2023-11-01 added spi initializer for reb b board
2023-11-02 yes! coredump parsing is sorted.
2023-11-02 Firmware release v1.1.0
2023-11-02 a few updates to the release script
2023-11-02 added in a todo
2023-11-02 more todo updates
2023-11-02 added better 404
2023-11-03 added in some more troubleshooting code
2023-11-03 Firmware release v1.1.1
2023-11-03 indentation fix
2023-11-03 getting ready for the attempt
2023-11-03 conversion to mongoose server is almost complete.
2023-11-03 version bump
2023-11-03 big todo update
2023-11-03 updated ignore
2023-11-03 fixed a wifi include name conflict
2023-11-03 first pass of using mongoose connection for auth
2023-11-03 re-aded the modified-since check
2023-11-03 redundant ota without async
2023-11-03 big first draft of the user configurable https
2023-11-03 typo oops
2023-11-04 added guard rails around ota and message sending
2023-11-06 a couple minor dev changes
2023-11-06 ignoring lib/ folders
2023-11-06 gulp working on mac now
2023-11-06 gulp upgraded to CJS style now
2023-11-06 new version algo from stack overflow
2023-11-07 added a few todos
2023-11-07 new rgb board checks out!
2023-11-17 added in microdebug library
2023-11-17 ssl UI is working, but not on the backend. shelved.
2023-11-17 added todo
2023-11-17 now scrolling to alerts.
2023-11-17 made site bigger on larger browsers
2023-11-17 fixed python path.
2023-11-17 semantic versioning fix from stackoverflow works.
2023-11-17 added a 'framerate' metric for loops per second
2023-11-17 framerate update and some ui fixes
2023-11-17 worked more on ssl, hit a wall
2023-11-17 working on the updated arduinomongoose library
2023-11-19 boards and firmware moved to their own repos.
